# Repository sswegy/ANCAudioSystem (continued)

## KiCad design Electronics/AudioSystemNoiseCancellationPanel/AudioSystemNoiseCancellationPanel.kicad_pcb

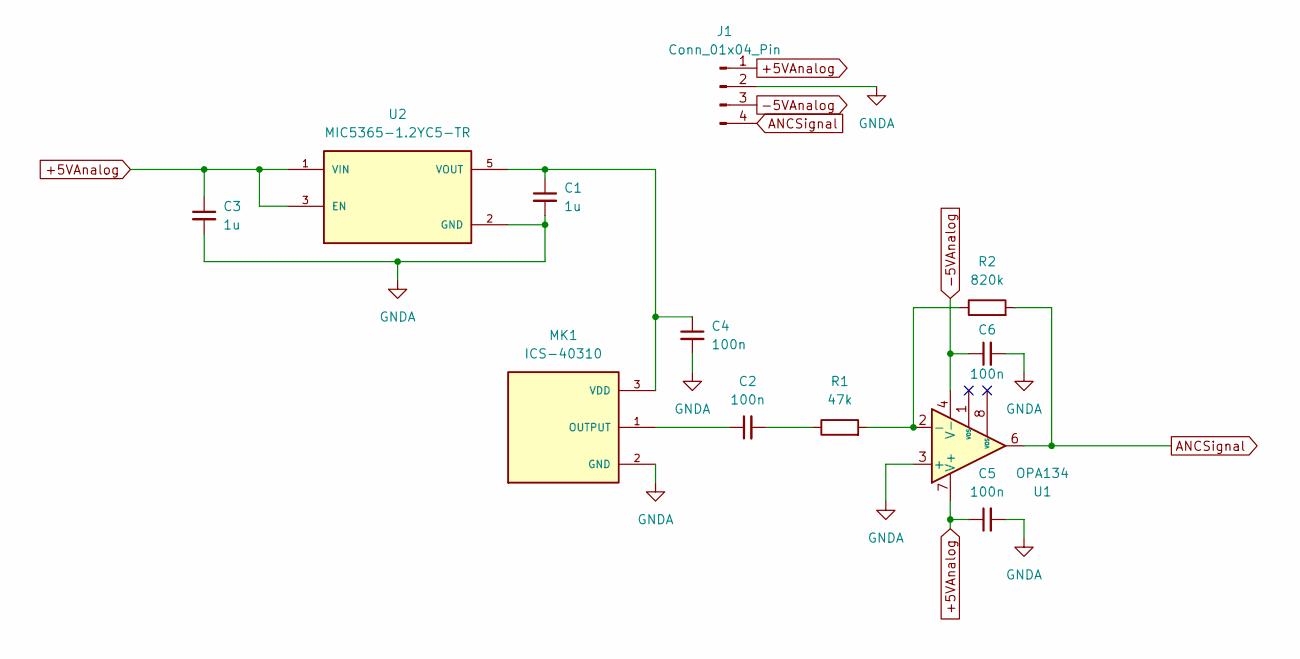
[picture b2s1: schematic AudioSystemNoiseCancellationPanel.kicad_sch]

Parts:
C1, C3: 1u; C_0805_2012Metric_Pad1.18x1.45mm_HandSolder
C2, C4, C5, C6: 100n; C_0805_2012Metric_Pad1.18x1.45mm_HandSolder
J1: Conn_01x04_Pin; 4_Pad_Connector
MK1: ICS-40310; MIC_ICS-40310; PARTREV 1.2
R1: 47k; R_0805_2012Metric_Pad1.20x1.40mm_HandSolder
R2: 820k; R_0805_2012Metric_Pad1.20x1.40mm_HandSolder
U1: OPA134; OPA134UA
U2: MIC5365-1.2YC5-TR; PARTREV 3.1 - July 16, 2013

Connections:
+5VAnalog: C3.1, C5.1, J1.1, U1.7 (V+), U2.1 (VIN), U2.3 (EN)
-5VAnalog: C6.1, J1.3, U1.4 (V-)
ANCSignal: J1.4, R2.2, U1.6
GNDA: C1.2, C3.2, C4.2, C5.2, C6.2, J1.2, MK1.2 (GND), U1.3 (+), U2.2 (GND)
unnamed: C2.2, R1.1
unnamed: C2.1, MK1.1 (OUTPUT)
unnamed: C1.1, C4.1, MK1.3 (VDD), U2.5 (VOUT)
unnamed: R1.2, R2.1, U1.2 (-)

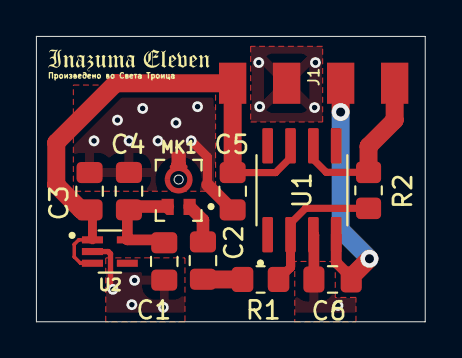
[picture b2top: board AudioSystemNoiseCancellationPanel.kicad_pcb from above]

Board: 2 copper layers, 21.6 x 15.9 mm, 12 parts (0 on the bottom side), 8 nets.

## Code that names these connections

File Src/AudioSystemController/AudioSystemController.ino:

#include <Wire.h>
#include <ESP_I2S.h>
#include <BluetoothA2DPSinkQueued.h>
#include <LiquidCrystal_I2C.h>
//#include "DebugTools.h"


#define I2C_SCL 17
#define I2C_SDA 16

#define I2S_SCK 22
#define I2S_WS 25
#define I2S_SD 26

#define PLAY 19
#define NEXT 18
#define PREV 21

#define AUX_LEFT 34
#define AUX_RIGHT 35

#define LCD_I2C_ADDRESS 0x27
#define LCD_DISPLAY_WIDTH 20
#define DISPLAY_SCROLL_INTERVAL_MS 250

#define BUTTON_DEBOUNCE_DELAY_MS 70

#define BLUETOOTH_DEVICE_NAME "InazumaEleven"

I2SClass i2s;
BluetoothA2DPSinkQueued a2dp_sink(i2s);
LiquidCrystal_I2C lcd(LCD_I2C_ADDRESS, 20, 4);

String currentSongTitle;
String currentSongArtist;
String currentSongAlbum;

esp_avrc_playback_stat_t playbackState;
volatile bool bluetoothEnabled = true;

struct ScrollState 
{
  int scrollIndex = 0;
  unsigned long previousMillis = 0;
};
ScrollState titleScrollState;
ScrollState artistScrollState;
ScrollState albumScrollState;

struct ButtonState 
{
  bool currentState;
  bool lastReading;
  unsigned long lastDebounceTime; 
};
ButtonState playButtonState = {false, false, 0};
ButtonState nextButtonState = {false, false, 0};
ButtonState prevButtonState = {false, false, 0};

void IRAM_ATTR toggleBluetooth()
{
  bluetoothEnabled = !(digitalRead(AUX_LEFT) || digitalRead(AUX_RIGHT));
  if (bluetoothEnabled)
    a2dp_sink.start(BLUETOOTH_DEVICE_NAME);
  else
   a2dp_sink.end();
}

void setup() 
{
  Serial.begin(115200);

  pinMode(AUX_LEFT, INPUT);
  pinMode(AUX_RIGHT, INPUT);
  attachInterrupt(AUX_LEFT, toggleBluetooth, CHANGE);
  attachInterrupt(AUX_RIGHT, toggleBluetooth, CHANGE);

  pinMode(PLAY, INPUT);
  pinMode(NEXT, INPUT);
  pinMode(PREV, INPUT);

  Wire.setPins(I2C_SDA, I2C_SCL);
  lcd.init();                      
  lcd.backlight();

  a2dp_sink.set_avrc_rn_track_change_callback([](uint8_t *id){
    currentSongTitle = "                    ";
    currentSongArtist = "                    ";
    currentSongAlbum = "                    ";
    lcd.clear();
  });
  a2dp_sink.set_avrc_metadata_attribute_mask(ESP_AVRC_MD_ATTR_TITLE | ESP_AVRC_MD_ATTR_ARTIST 
  | ESP_AVRC_MD_ATTR_ALBUM);
  a2dp_sink.set_avrc_metadata_callback([](uint8_t metadata_id, const uint8_t *metadata_value){
    switch (metadata_id) 
    {
      case ESP_AVRC_MD_ATTR_TITLE:
        currentSongTitle = (const char*)metadata_value;
        break;
      case ESP_AVRC_MD_ATTR_ARTIST:
        currentSongArtist = (const char*)metadata_value;
        break;
      case ESP_AVRC_MD_ATTR_ALBUM:
        currentSongAlbum = (const char*)metadata_value;
        break;
      default:
        break;
    }
  });
  a2dp_sink.set_avrc_rn_playstatus_callback([](esp_avrc_playback_stat_t playback_state){
    playbackState = playback_state;
  });
  
  i2s.setPins(I2S_SCK, I2S_WS, I2S_SD);
  i2s.begin(I2S_MODE_STD, 44100, I2S_DATA_BIT_WIDTH_16BIT, I2S_SLOT_MODE_STEREO, I2S_STD_SLOT_BOTH);
  a2dp_sink.start(BLUETOOTH_DEVICE_NAME);
}

void loop() 
{
  if (bluetoothEnabled)
  {
    if (a2dp_sink.is_connected())
    {
      printFormattedSongData();
      if (debounceButton(PLAY, BUTTON_DEBOUNCE_DELAY_MS, playButtonState))
      {
        if (playbackState == ESP_AVRC_PLAYBACK_PLAYING)
          a2dp_sink.pause();
        else if (playbackState == ESP_AVRC_PLAYBACK_PAUSED)
          a2dp_sink.play();
      }
      else if (debounceButton(NEXT, BUTTON_DEBOUNCE_DELAY_MS, nextButtonState))
        a2dp_sink.next();
      else if (debounceButton(PREV, BUTTON_DEBOUNCE_DELAY_MS, prevButtonState))
        a2dp_sink.previous();
    }
    else
    {   
      lcd.clear();
      lcd.setCursor(0, 0);
      lcd.print("Bluetooth ON");
      lcd.setCursor(0, 1);
      lcd.print("Not connected");
    }
  }
  else
  {
    lcd.clear();
    lcd.setCursor(0, 0);
    lcd.print("Bluetooth OFF");
  }
}

bool debounceButton(uint8_t buttonPin, unsigned long debounceDelay, ButtonState &state) 
{
  bool reading = digitalRead(buttonPin);
  if (reading != state.lastReading)
    state.lastDebounceTime = millis();

  if ((millis() - state.lastDebounceTime) > debounceDelay)
    if (reading != state.currentState)
      state.currentState = reading;

  state.lastReading = reading;
  return state.currentState;
}

String repeatString(String text, int times) 
{
  String result = "";
  for (int i = 0; i < times; i++)
    result += text;
  return result;
}

void displayStaticAndScrollData(String dataText, int row, int displayWidth, int interval, ScrollState &state) 
{
  if (dataText.length() > displayWidth) 
  {
    dataText += "  ";
    unsigned long currentMillis = millis();
    if (currentMillis - state.previousMillis >= interval) 
    {
      state.previousMillis = currentMillis;

      lcd.setCursor(0, row);
      lcd.print(repeatString(" ", displayWidth));

      String displayText;
      if (state.scrollIndex + displayWidth <= dataText.length())
        displayText = dataText.substring(state.scrollIndex, state.scrollIndex + displayWidth);
      else
        displayText = dataText.substring(state.scrollIndex) + dataText.substring(0, (state.scrollIndex + displayWidth) % dataText.length());

      lcd.setCursor(0, row);
      lcd.print(displayText);

      state.scrollIndex = (state.scrollIndex + 1) % dataText.length();
    }
  } 
  else 
  {
    lcd.setCursor(0, row);
    lcd.print(dataText);
  }
}

void printFormattedSongData()
{
  displayStaticAndScrollData(currentSongTitle, 0, LCD_DISPLAY_WIDTH, DISPLAY_SCROLL_INTERVAL_MS, titleScrollState);
  displayStaticAndScrollData(currentSongArtist, 1, LCD_DISPLAY_WIDTH, DISPLAY_SCROLL_INTERVAL_MS, artistScrollState);
  displayStaticAndScrollData(currentSongAlbum, 2, LCD_DISPLAY_WIDTH, DISPLAY_SCROLL_INTERVAL_MS, albumScrollState);
}

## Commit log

2024-10-14 add kicad main panel schematic
2024-10-14 gitignore working
2024-10-14 add audio system block diagram v2
2024-10-17 added filter/eq panel, small fixes for main panel
2024-10-17 created noise cancellation panel, added a custom symbol library to project
2024-10-17 fixed symbol lab problem, added symbols to all ics
2024-10-22 changed all panels input and output audio interfaces, added noisecancellation panel
2024-10-31 added code debug function namespace, fixed eq-panel resistor values
2024-11-06 added full audio system schematic (not completed)
2024-11-13 a2dp sink, avrcp data displaying and animating on lcd done
2024-11-18 progress check
2024-11-18 deleted unnecessary schematics
2024-12-11 power supply schematic possibly done
2024-12-16 complete head unit schematic
2024-12-21 added next/play/prev buttons (hardware and software)
2024-12-24 added all resistor footprints
2024-12-26 added capacitor footprints and all known elements serial numbers
2024-12-27 added all footprints
2024-12-28 organize footprints by purpose
2025-01-04 footprint placement part 1
2025-01-13 footprint placement possibly done, minor schematic changes
2025-01-18 progress sync
2025-02-05 pcbs done
2025-02-05 add mounting holes to main pcb
2025-02-05 3dmodel changes
2025-02-09 done v.1
2025-03-11 sync latest
2025-05-02 button debounce fix, minor changes
